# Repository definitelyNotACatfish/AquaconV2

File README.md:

# Web based Aquarium LED controller
I didn't want to pay 200€ to buy a 6 channel LED PWM controller. So I invested 400€ and a half year to build it myself :)

## Keyfeatures
- 6 channels PWM controlled (For LEDs and other stuff like CO2 relay or PC fan to cool water surface
- Web based interface to set up channel independent scenarious
- Temperature controlled water surface cooling (Really cool in summer)
- SD card bootloader and ethernet based file transfer to SD card

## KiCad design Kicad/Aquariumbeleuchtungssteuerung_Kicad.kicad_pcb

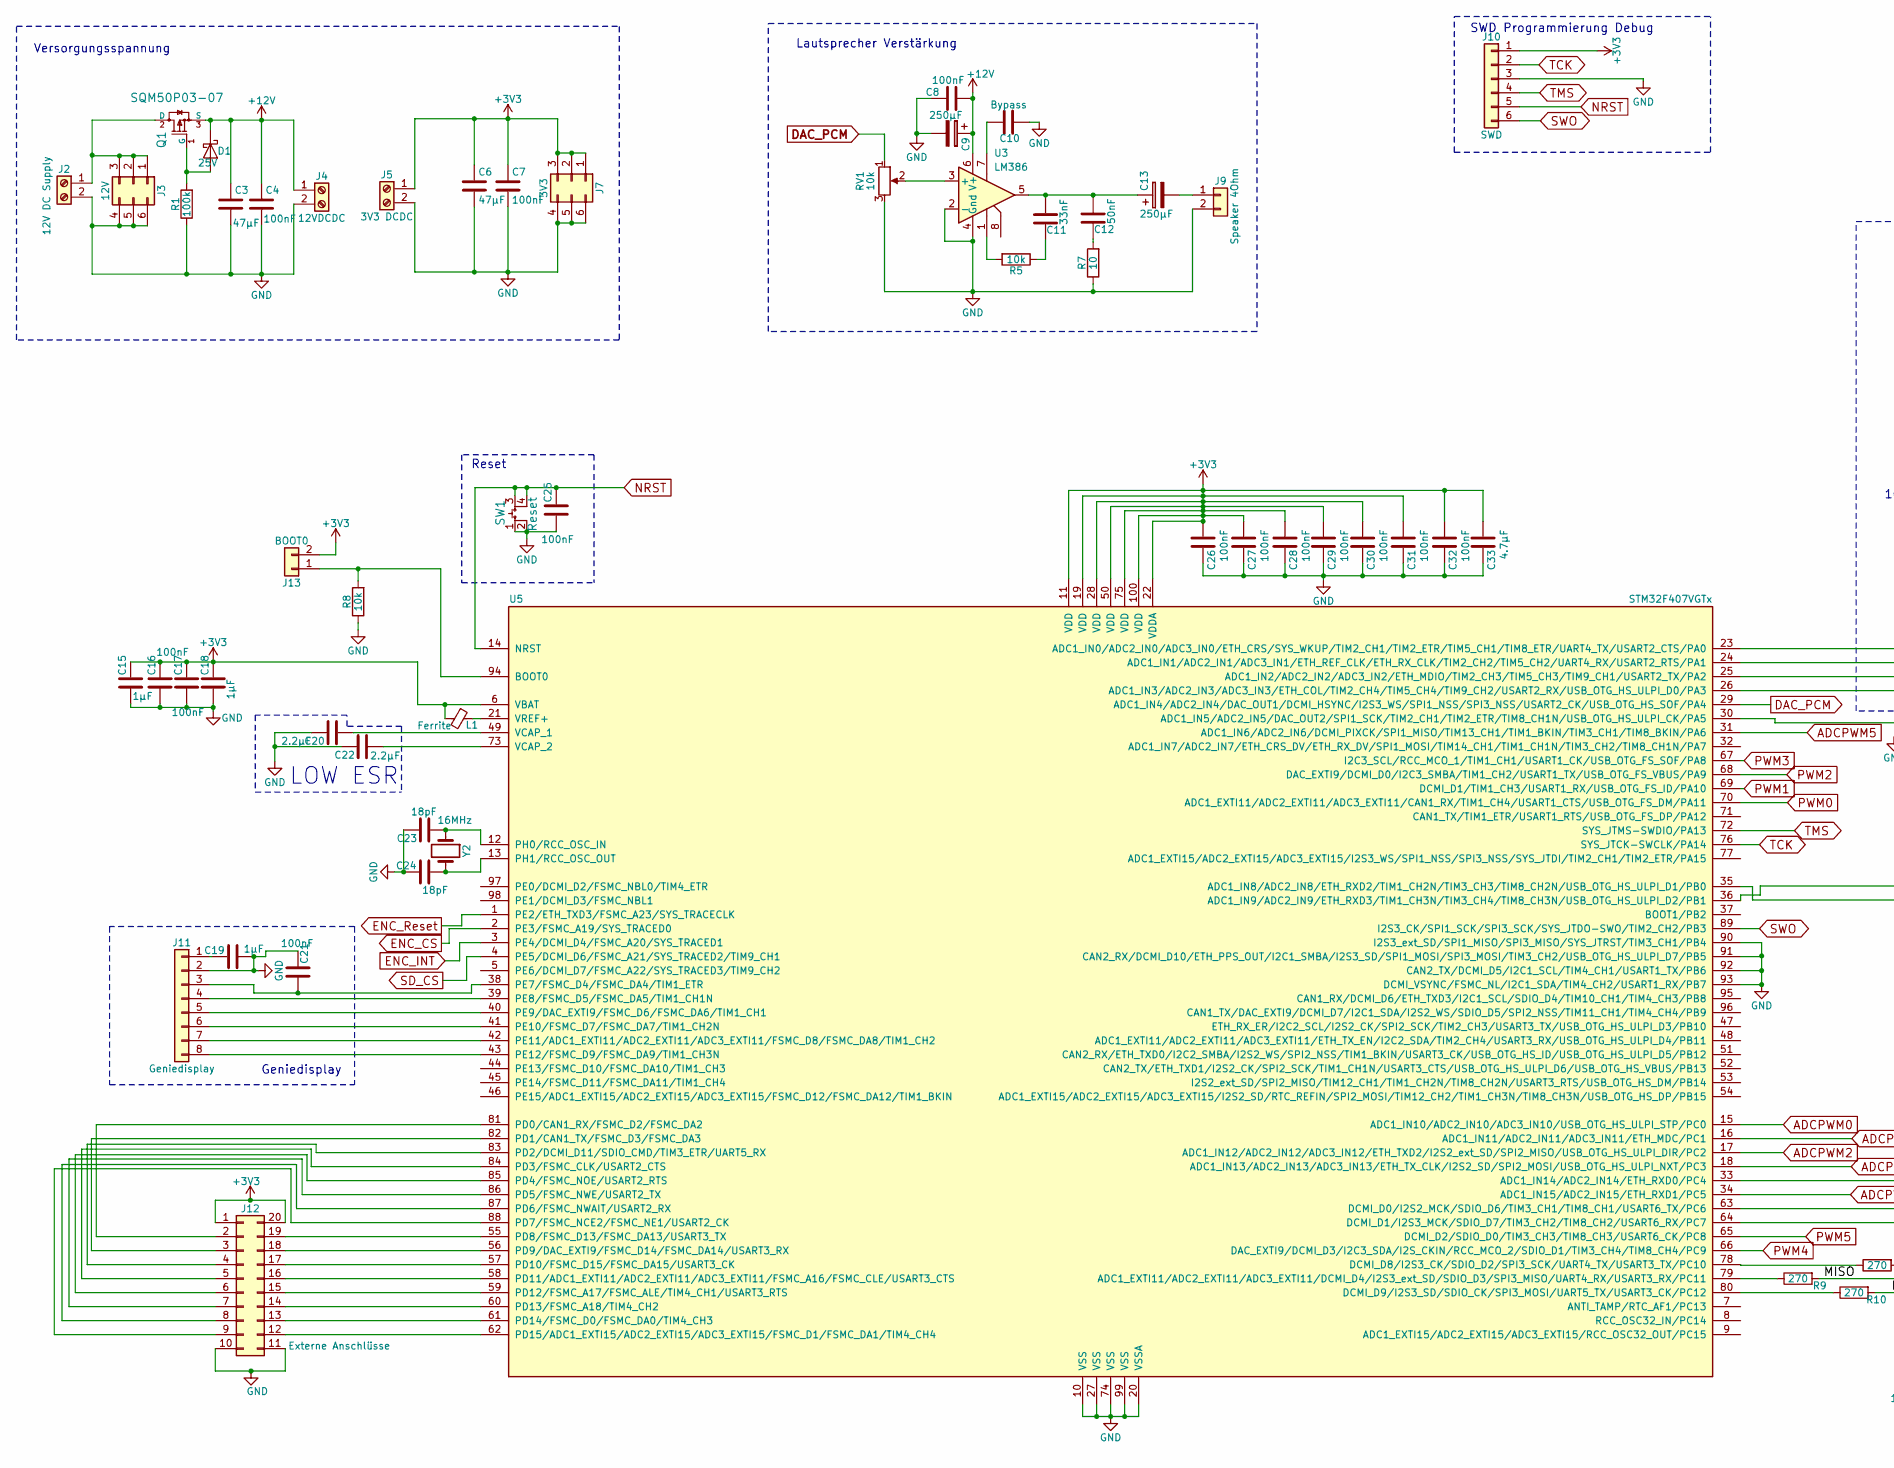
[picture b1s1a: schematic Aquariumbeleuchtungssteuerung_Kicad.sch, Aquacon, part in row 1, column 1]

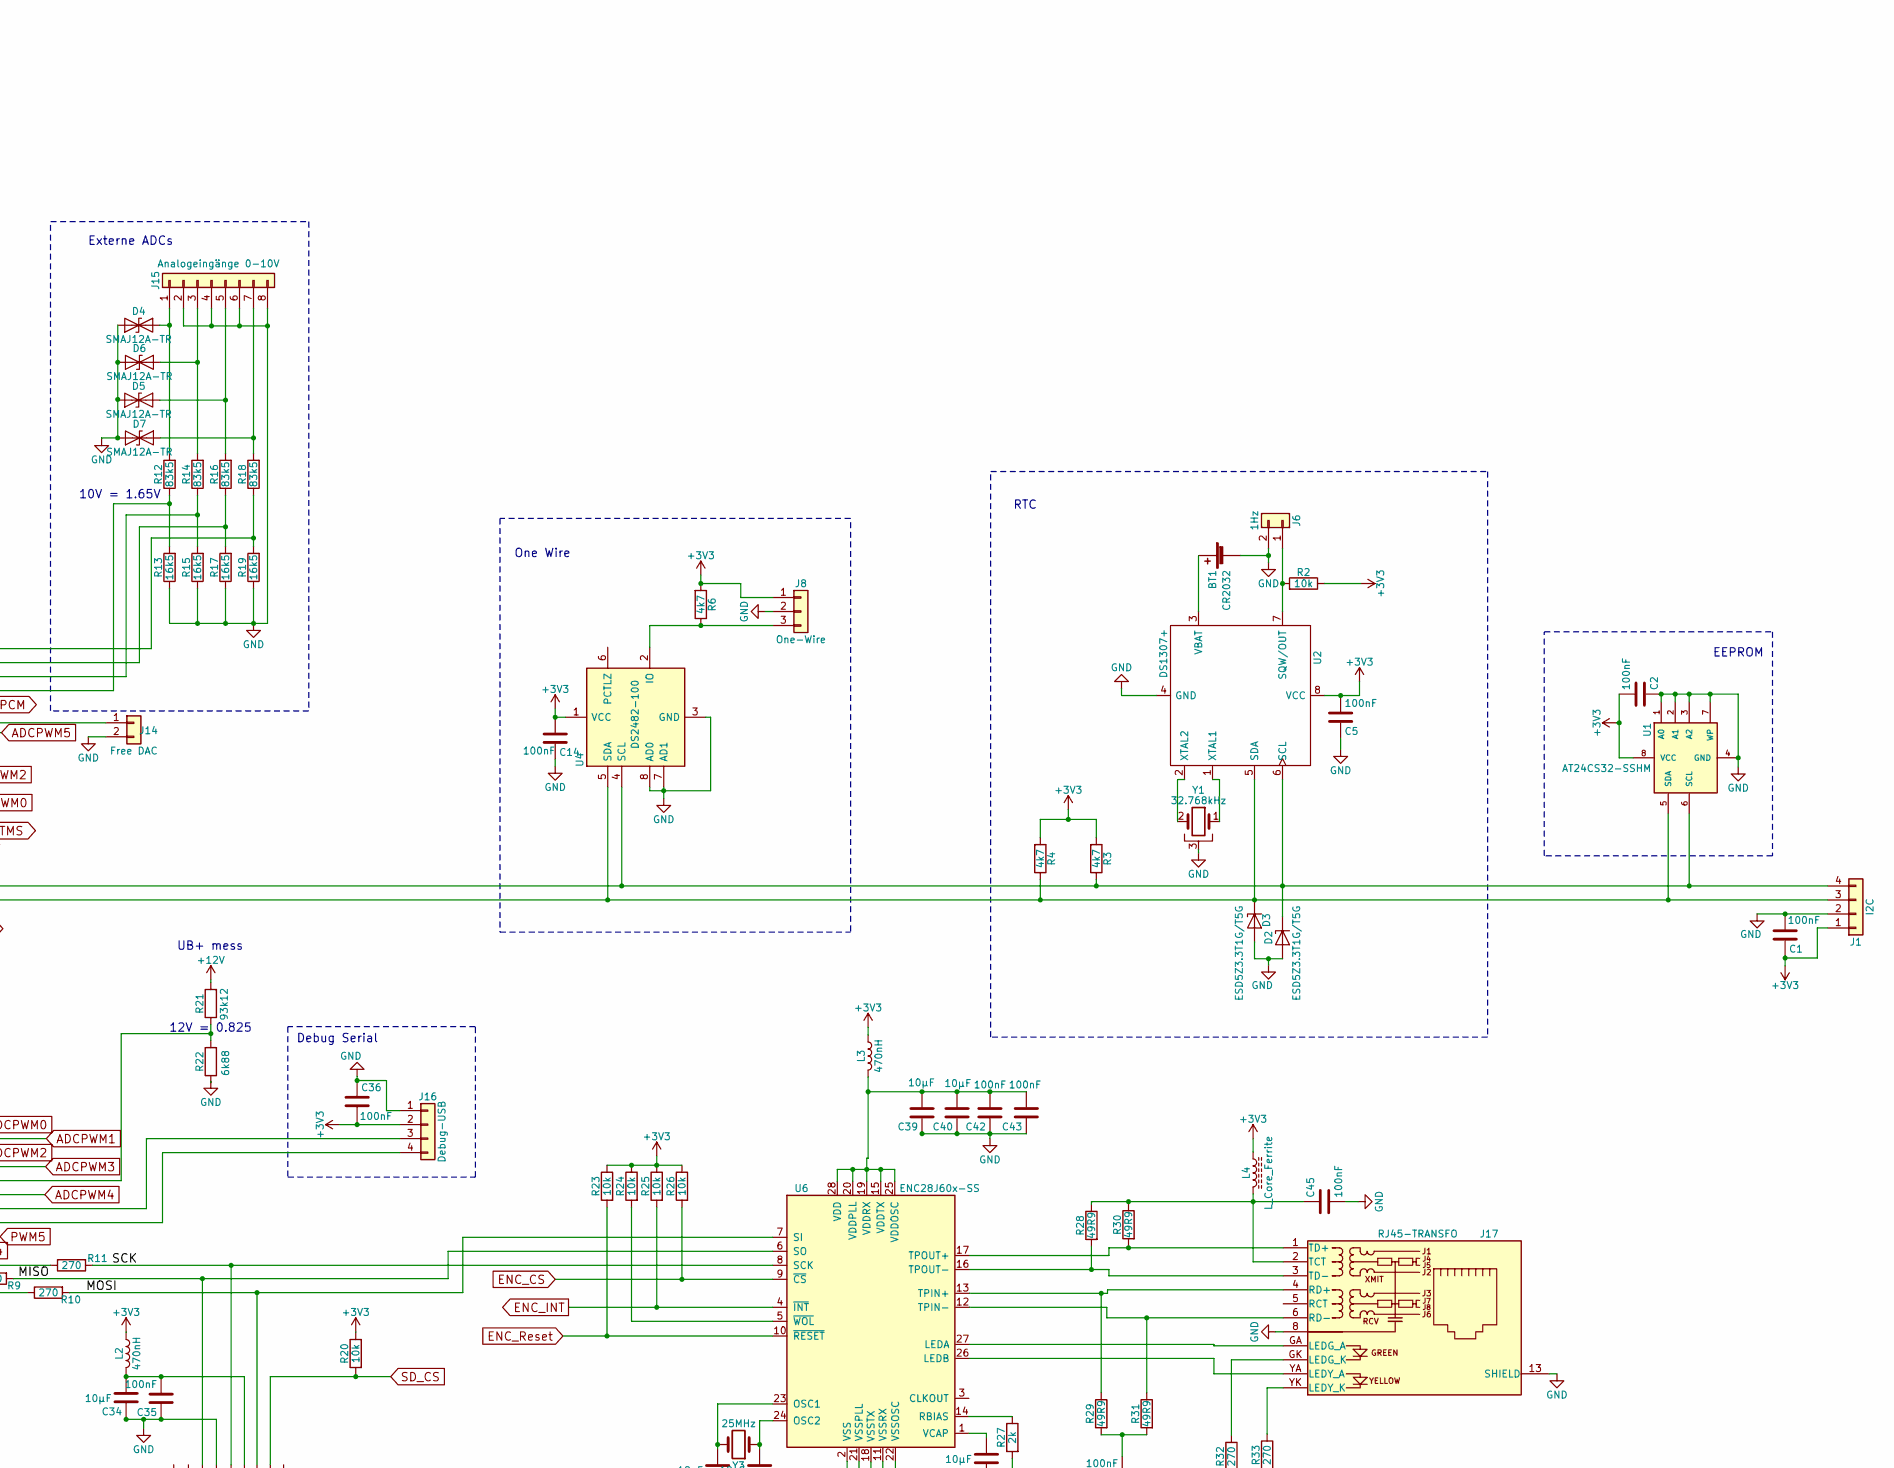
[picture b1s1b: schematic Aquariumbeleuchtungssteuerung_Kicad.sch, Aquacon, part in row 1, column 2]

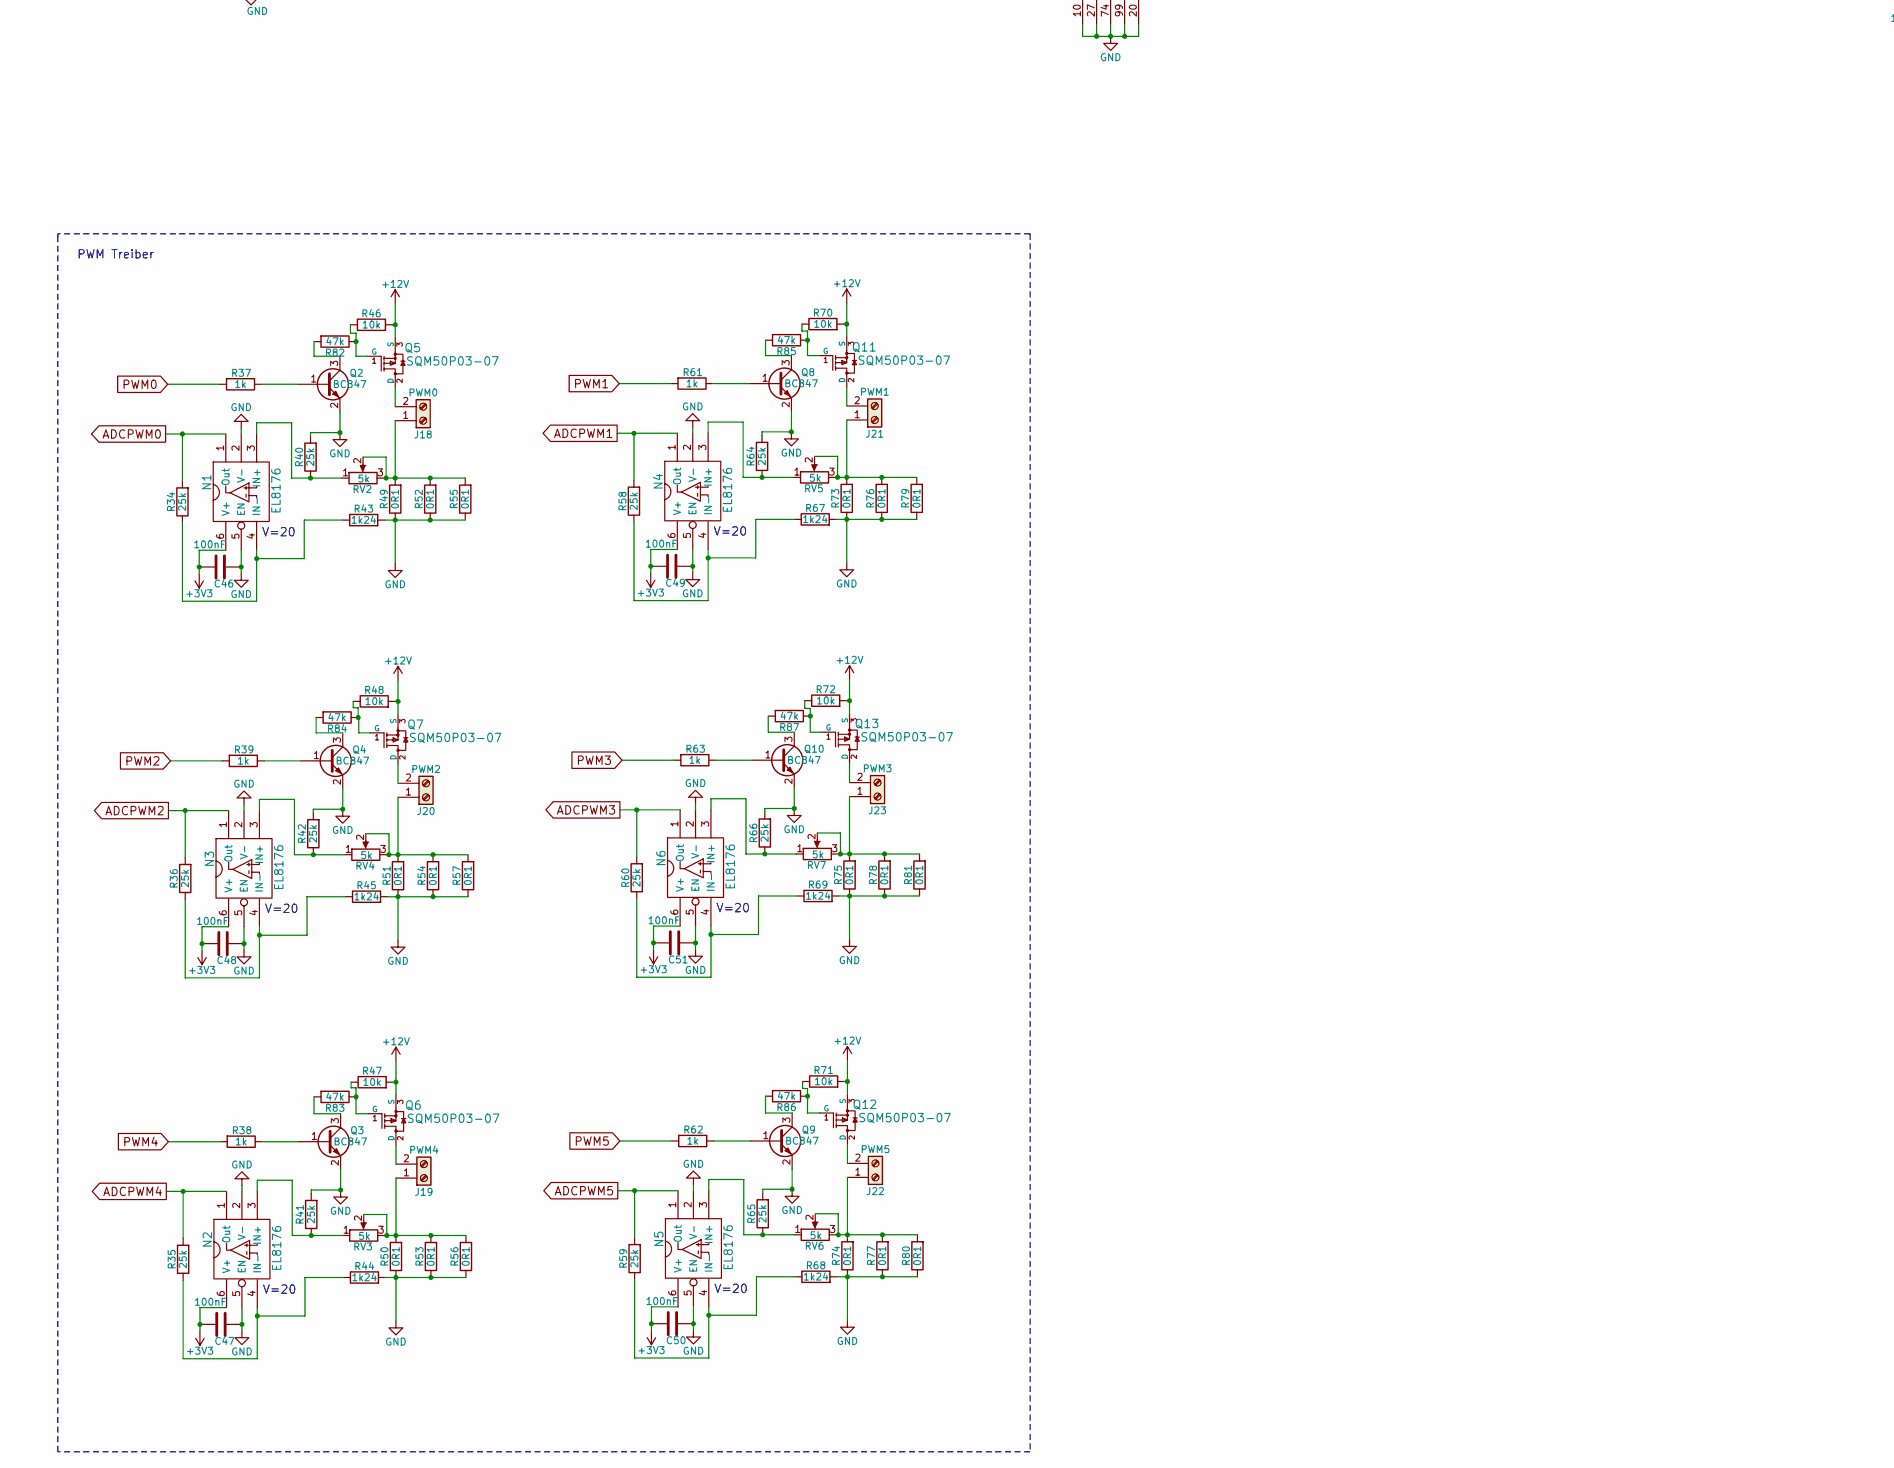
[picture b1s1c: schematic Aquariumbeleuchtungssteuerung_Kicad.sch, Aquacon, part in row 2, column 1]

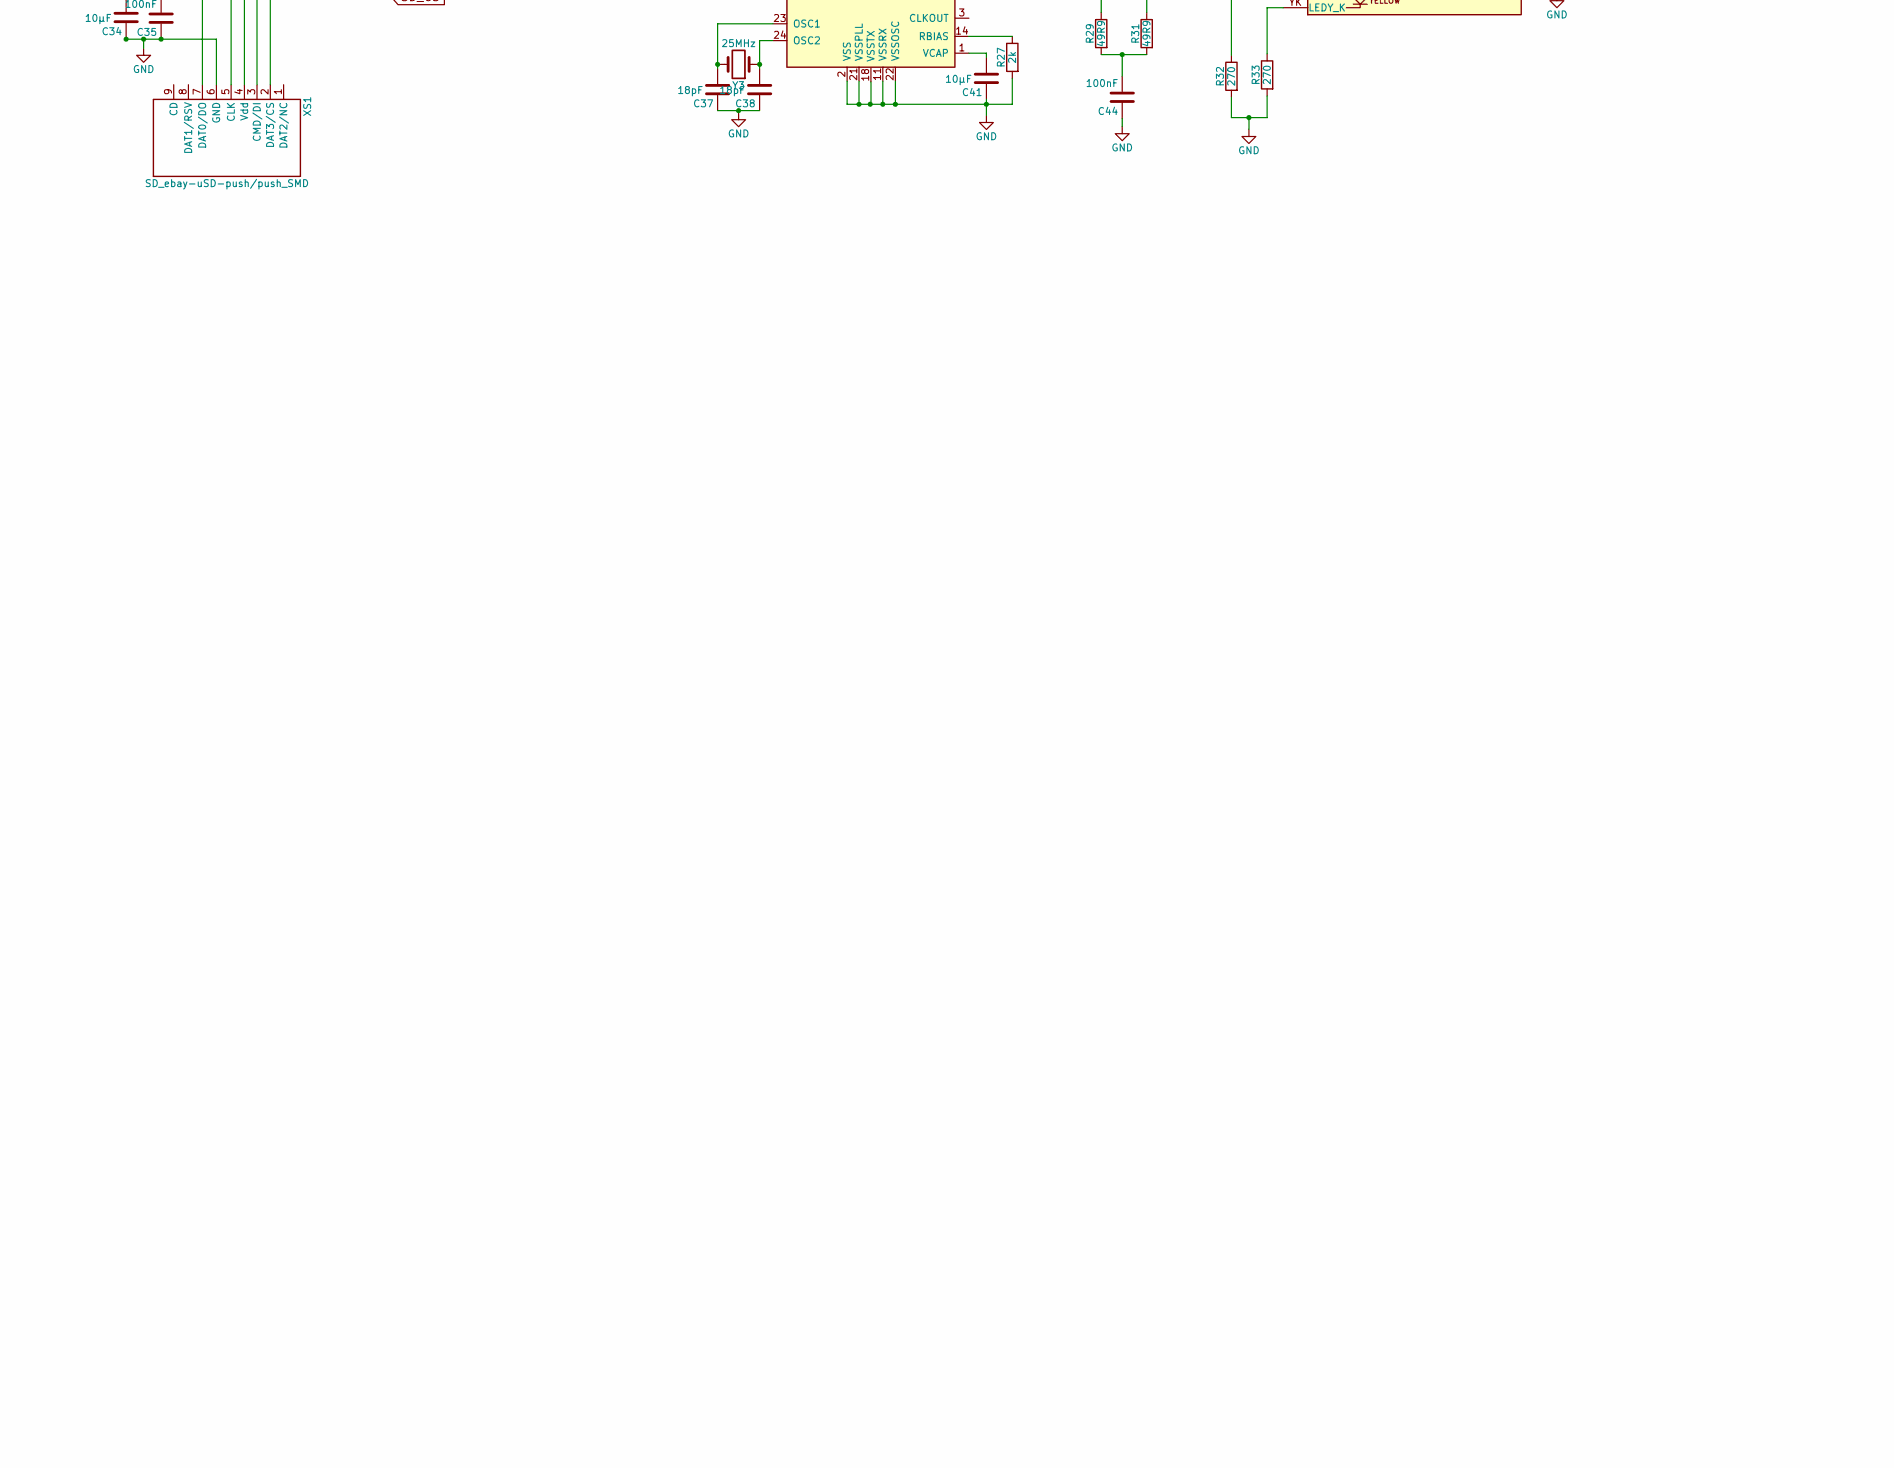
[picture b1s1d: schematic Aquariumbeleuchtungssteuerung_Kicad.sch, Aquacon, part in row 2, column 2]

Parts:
BT1: CR2032; Keystone_105_1x2430-CoinCell
C1, C2, C14, C21, C26, C27, C28, C29, C30, C31, C32, C36, C42, C43, C44, C45, C46, C47, C48, C49, C50, C51: 100nF; C_0603
C3, C6: 47µF; R_1206
C4, C5, C7, C8, C16, C17, C25: 100nF; C_0805
C9, C13: 250µF; CP_Tantalum_Case-X_EIA-7343-43_Reflow
C10: Bypass; C_0805
C11: 33nF; C_0805
C12: 50nF; C_0805
C15, C18, C19: 1µF; C_0805
C20, C22: 2.2µF; C_0805
C23, C24, C37, C38: 18pF; C_0603
C33: 4.7µF; C_0805
C34: 10µF; L_0805
C35: 100nF; L_0603
C39, C40, C41: 10µF; C_0805
D1: 25V; D_SOD-123
D2, D3: ESD5Z3.3T1G/T5G; D_SOD-523
D4, D5, D6, D7: SMAJ12A-TR; D_SMA
J1: I2C; Pin_Header_Straight_1x04_Pitch2.54mm
J2: 12V DC Supply; DECA_MB91_9.52mm_01X02
J3: 12V; Stiftleiste-2x3x2.54mm
J4: 12VDCDC; Pin_Header_Straight_1x02_Pitch2.54mm
J5: 3V3 DCDC; Pin_Header_Straight_1x02_Pitch2.54mm
J6: 1Hz; Pin_Header_Straight_1x02_Pitch2.54mm
J7: 3V3; Stiftleiste-2x3x2.54mm
J8: One-Wire; Pin_Header_Straight_1x03_Pitch2.54mm
J9: Speaker 4Ohm; Pin_Header_Straight_1x02_Pitch2.54mm
J10: SWD; Pin_Header_Straight_1x06_Pitch2.54mm
J11: Geniedisplay; Pin_Header_Straight_1x08_Pitch2.54mm
J12: Externe Anschlüsse; Stiftleiste_02x10
J13: BOOT0; GS2
J14: Free DAC; Pin_Header_Straight_1x02_Pitch2.54mm
J15: Analogeingänge 0-10V; TerminalBlock_bornier-8_P5.08mm
J16: Debug-USB; Pin_Header_Straight_1x04_Pitch2.54mm
J17: RJ45-TRANSFO; RJ45_TRANSFO
J18: PWM0; Phoenix-D-FRONT-2.5Vx2
J19: PWM4; Phoenix-D-FRONT-2.5Vx2
J20: PWM2; Phoenix-D-FRONT-2.5Vx2
J21: PWM1; Phoenix-D-FRONT-2.5Vx2
J22: PWM5; Phoenix-D-FRONT-2.5Vx2
J23: PWM3; Phoenix-D-FRONT-2.5Vx2
L1: Ferrite; L_0805
L2: 470nH; L_0805
L3: 470nH; L_0603
L4: L_Core_Ferrite; L_0603
N1, N2, N3, N4, N5, N6: EL8176; SOT-23-6_Handsoldering
Q1, Q5, Q6, Q7, Q11, Q12, Q13: SQM50P03-07; TO-263-2
Q2, Q3, Q4, Q8, Q9, Q10: BC847; SOT-23
R1: 100k; R_0805
R2, R8, R20, R23, R24, R25, R26: 10k; R_0603
R3, R4, R6: 4k7; R_0603
R5, R46, R47, R48, R70, R71, R72: 10k; R_0805
R7: 10; R_0805
R9, R10, R11, R32, R33: 270; R_0603
R12, R14, R16, R18: 83k5; R_0603
R13, R15, R17, R19: 16k5; R_0603
R21: 93k12; R_0805
R22: 6k88; R_0805
R27: 2k; R_0603
R28, R29, R30, R31: 49R9; R_0603
R34, R35, R36, R40, R41, R42, R58, R59, R60, R64, R65, R66: 25k; R_0603
R37, R38, R39, R61, R62, R63: 1k; R_0603
R43, R44, R45, R67, R68, R69: 1k24; R_0603
R49, R50, R51, R52, R53, R54, R55, R56, R57, R73, R74, R75, R76, R77, R78, R79, R80, R81: 0R1; R_1206
R82, R83, R84, R85, R86, R87: 47k; R_0603
RV1: 10k; Potentiometer_Trimmer_Bourns_3224J
RV2, RV3, RV4, RV5, RV6, RV7: 5k; Potentiometer_Trimmer_Bourns_3224J
SW1: Reset; SW_TH_Tactile_Omron_B3F-10xx
U1: AT24CS32-SSHM; SOIC-8_3.9x4.9mm_Pitch1.27mm
U2: DS1307+; SO-8_5.3x6.2mm_Pitch1.27mm
U3: LM386; DIP-8_W7.62mm_Socket
U4: DS2482-100; SOIC-8_3.9x4.9mm_Pitch1.27mm
U5: STM32F407VGTx; LQFP-100_14x14mm_Pitch0.5mm
U6: ENC28J60x-SS; SSOP-28_5.3x10.2mm_Pitch0.65mm
XS1: SD_ebay-uSD-push/push_SMD; Conn_uSDcard
Y1: 32.768kHz; Crystal_C38-LF_d3.0mm_l8.0mm_Horizontal_1EP_style2
Y2: 16MHz; Crystal_SMD_HC49-SD
Y3: 25MHz; Crystal_SMD_HC49-SD

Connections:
+3V3: C1.1, C2.2, C5.2, C6.1, C7.1, C14.2, C15.1, C16.1, C17.1, C18.1, C26.2, C27.2, C28.2, C29.2, C30.2, C31.2, C32.2, C33.2, C36.2, C46.2, C47.2, C48.2, C49.2, C50.2, C51.2, J1.1, J5.1, J7.1, J7.2, J7.3, J8.1, J10.1, J12.1, J12.20, J13.2, J16.2, L1.2, L2.1, L3.1, L4.1, N1.6 (V+), N2.6 (V+), N3.6 (V+), N4.6 (V+), N5.6 (V+), N6.6 (V+), R2.1, R3.2, R4.2, R6.2, R20.1, R23.1, R24.1, R25.1, R26.1, U1.8 (VCC), U2.8 (VCC), U4.1 (VCC), U5.6 (VBAT), U5.11 (VDD), U5.19 (VDD), U5.22 (VDDA), U5.28 (VDD), U5.50 (VDD), U5.75 (VDD), U5.100 (VDD)
+12V: C3.1, C4.1, C8.1, C9.1, D1.1 (K), J4.1, Q1.3 (S), Q5.3 (S), Q6.3 (S), Q7.3 (S), Q11.3 (S), Q12.3 (S), Q13.3 (S), R21.2, R46.2, R47.2, R48.2, R70.2, R71.2, R72.2, U3.6 (V+)
/MISO: R9.2, U6.6 (SO), XS1.7 (DAT0/DO)
/MOSI: R10.2, U6.7 (SI), XS1.3 (CMD/DI)
/SCK: R11.2, U6.8 (SCK), XS1.5 (CLK)
ADCPWM0: N1.1 (Out), R34.2, U5.15 (ADC1_IN10/ADC2_IN10/ADC3_IN10/USB_OTG_H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)
ADCPWM1: N4.1 (Out), R58.2, U5.16 (ADC1_IN11/ADC2_IN11/ADC3_IN11/ETH_MDC/P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)
ADCPWM2: N3.1 (Out), R36.2, U5.17 (ADC1_IN12/ADC2_IN12/ADC3_IN12/ETH_TXD2/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)
ADCPWM3: N6.1 (Out), R60.2, U5.18 (ADC1_IN13/ADC2_IN13/ADC3_IN13/ETH_TX_CL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)
ADCPWM4: N2.1 (Out), R35.2, U5.34 (ADC1_IN15/ADC2_IN15/ETH_RXD1/PC5)
ADCPWM5: N5.1 (Out), R59.2, U5.31 (ADC1_IN6/ADC2_IN6/DCMI_PIXCK/SPI1_MISO/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)
DAC_PCM: RV1.1, U5.29 (ADC1_IN4/ADC2_IN4/DAC_OUT1/DCMI_HSYNC/I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)
ENC_CS: R26.2, U5.2 (PE3/FSMC_A19/SYS_TRACED0), U6.9 (~CS)
ENC_INT: R25.2, U5.3 (PE4/DCMI_D4/FSMC_A20/SYS_TRACED1), U6.4 (~INT)
ENC_Reset: R23.2, U5.1 (PE2/ETH_TXD3/FSMC_A23/SYS_TRACECLK), U6.10 (~RESET)
GND: BT1.2 (-), C1.2, C2.1, C3.2, C4.2, C5.1, C6.2, C7.2, C8.2, C9.2, C10.2, C14.1, C15.2, C16.2, C17.2, C18.2, C19.2, C20.1, C21.1, C22.1, C23.1, C24.1, C25.2, C26.1, C27.1, C28.1, C29.1, C30.1, C31.1, C32.1, C33.1, C34.1, C35.1, C36.1, C37.1, C38.1, C39.1, C40.1, C41.1, C42.1, C43.1, C44.1, C45.2, C46.1, C47.1, C48.1, C49.1, C50.1, C51.1, D2.2 (A), D3.2 (A), D4.1 (A1), D5.1 (A1), D6.1 (A1), D7.1 (A1), J1.2, J2.2, J3.4, J3.5, J3.6, J4.2, J5.2, J6.2, J7.4, J7.5, J7.6, J8.2, J9.2, J10.3, J11.2, J12.10, J12.11, J14.2, J15.2, J15.4, J15.6, J15.8, J16.1, J17.8, J17.13 (SHIELD), N1.2 (V-), N1.5 (EN), N2.2 (V-), N2.5 (EN), N3.2 (V-), N3.5 (EN), N4.2 (V-), N4.5 (EN), N5.2 (V-), N5.5 (EN), N6.2 (V-), N6.5 (EN), Q2.2 (E), Q3.2 (E), Q4.2 (E), Q8.2 (E), Q9.2 (E), Q10.2 (E), R1.1, R7.1, R8.1, R13.1, R15.1, R17.1, R19.1, R22.1, R27.2, R32.2, R33.2, R40.2, R41.2, R42.2, R43.2, R44.2, R45.2, R49.1, R50.1, R51.1, R52.1, R53.1, R54.1, R55.1, R56.1, R57.1, R64.2, R65.2, R66.2, R67.2, R68.2, R69.2, R73.1, R74.1, R75.1, R76.1, R77.1, R78.1, R79.1, R80.1, R81.1, RV1.3, SW1.1, SW1.2, U1.1 (A0), U1.2 (A1), U1.3 (A2), U1.4 (GND), U1.7 (WP), U2.4 (GND), U3.2 (-), U3.4 (Gnd), U4.3 (GND), U4.7 (AD1), U4.8 (AD0), U5.10 (VSS), U5.20 (VSSA), U5.27 (VSS), U5.74 (VSS), U5.90 (I2S3_ext_SD/SPI1_MISO/SPI3_MISO/SYS_JTR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), U5.91 (CAN2_RX/DCMI_D10/ETH_PPS_OUT/I2C1_SMBA/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), U5.92 (CAN2_TX/DCMI_D5/I2C1_SCL/TIM4_CH1/USART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), U5.93 (DCMI_VSYNC/FSMC_NL/I2C1_SDA/TIM4_CH2/US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), U5.99 (VSS), U6.2 (VSS), U6.11 (VSSRX), U6.18 (VSSTX), U6.21 (VSSPLL), U6.22 (VSSOSC), XS1.6 (GND), Y1.3
NRST: C25.1, J10.5, SW1.3, SW1.4, U5.14 (NRST)
unnamed: BT1.1 (+), U2.3 (VBAT)
unnamed: C10.1, U3.7
unnamed: C11.1, R5.1
unnamed: C11.2, C12.2, C13.1, U3.5
unnamed: C12.1, R7.2
unnamed: C13.2, J9.1
unnamed: C19.1, J11.1
unnamed: C20.2, U5.49 (VCAP_1)
unnamed: C21.2, J11.3, U5.38 (PE7/FSMC_D4/FSMC_DA4/TIM1_ETR)
unnamed: C22.2, U5.73 (VCAP_2)
unnamed: C23.2, U5.12 (PH0/RCC_OSC_IN), Y2.1
unnamed: C24.2, U5.13 (PH1/RCC_OSC_OUT), Y2.2
unnamed: C34.2, C35.2, L2.2, XS1.4 (Vdd)
unnamed: C37.2, U6.23 (OSC1), Y3.2
unnamed: C38.2, U6.24 (OSC2), Y3.1
unnamed: C39.2, C40.2, C42.2, C43.2, L3.2, U6.15 (VDDTX), U6.19 (VDDRX), U6.20 (VDDPLL), U6.25 (VDDOSC), U6.28 (VDD)
unnamed: C41.2, U6.1 (VCAP)
unnamed: C44.2, R29.2, R31.2
unnamed: C45.1, J17.2 (TCT), L4.2, R28.1, R30.1
unnamed: D1.2 (A), Q1.1 (G), R1.2
unnamed: D2.1 (K), J1.4, R3.1, U1.6 (SCL), U2.6 (SCL), U4.4 (SCL), U5.36 (ADC1_IN9/ADC2_IN9/ETH_RXD3/TIM1_CH3N/TI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)
unnamed: D3.1 (K), J1.3, R4.1, U1.5 (SDA), U2.5 (SDA), U4.5 (SDA), U5.35 (ADC1_IN8/ADC2_IN8/ETH_RXD2/TIM1_CH2N/TI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)
unnamed: D4.2 (A2), J15.1, R12.2
unnamed: D5.2 (A2), J15.5, R16.2
unnamed: D6.2 (A2), J15.3, R14.2
unnamed: D7.2 (A2), J15.7, R18.2
unnamed: J2.1, J3.1, J3.2, J3.3, Q1.2 (D)
unnamed: J6.1, R2.2, U2.7 (SQW/OUT)
unnamed: J8.3, R6.1, U4.2 (IO)
unnamed: J11.4, U5.39 (PE8/FSMC_D5/FSMC_DA5/TIM1_CH1N)
unnamed: J11.5, U5.40 (PE9/DAC_EXTI9/FSMC_D6/FSMC_DA6/TIM1_CH1)
unnamed: J11.6, U5.41 (PE10/FSMC_D7/FSMC_DA7/TIM1_CH2N)
unnamed: J11.7, U5.42 (PE11/ADC1_EXTI11/ADC2_EXTI11/ADC3_EXTI1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)
unnamed: J11.8, U5.43 (PE12/FSMC_D9/FSMC_DA9/TIM1_CH3N)
unnamed: J12.2, U5.81 (PD0/CAN1_RX/FSMC_D2/FSMC_DA2)
unnamed: J12.3, U5.82 (PD1/CAN1_TX/FSMC_D3/FSMC_DA3)
unnamed: J12.4, U5.83 (PD2/DCMI_D11/SDIO_CMD/TIM3_ETR/UART5_RX)
unnamed: J12.5, U5.84 (PD3/FSMC_CLK/USART2_CTS)
unnamed: J12.6, U5.85 (PD4/FSMC_NOE/USART2_RTS)
unnamed: J12.7, U5.86 (PD5/FSMC_NWE/USART2_TX)
unnamed: J12.8, U5.87 (PD6/FSMC_NWAIT/USART2_RX)
unnamed: J12.9, U5.88 (PD7/FSMC_NCE2/FSMC_NE1/USART2_CK)
unnamed: J12.12, U5.62 (PD15/ADC1_EXTI15/ADC2_EXTI15/ADC3_EXTI1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)
unnamed: J12.13, U5.61 (PD14/FSMC_D0/FSMC_DA0/TIM4_CH3)
unnamed: J12.14, U5.60 (PD13/FSMC_A18/TIM4_CH2)
unnamed: J12.15, U5.59 (PD12/FSMC_A17/FSMC_ALE/TIM4_CH1/USART3_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)
unnamed: J12.16, U5.58 (PD11/ADC1_EXTI11/ADC2_EXTI11/ADC3_EXTI1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)
unnamed: J12.17, U5.57 (PD10/FSMC_D15/FSMC_DA15/USART3_CK)
unnamed: J12.18, U5.56 (PD9/DAC_EXTI9/FSMC_D14/FSMC_DA14/USART3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)
unnamed: J12.19, U5.55 (PD8/FSMC_D13/FSMC_DA13/USART3_TX)
unnamed: J13.1, R8.2, U5.94 (BOOT0)
unnamed: J14.1, U5.30 (ADC1_IN5/ADC2_IN5/DAC_OUT2/SPI1_SCK/TIM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)
unnamed: J16.3, U5.63 (DCMI_D0/I2S2_MCK/SDIO_D6/TIM3_CH1/TIM8_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)
unnamed: J16.4, U5.64 (DCMI_D1/I2S3_MCK/SDIO_D7/TIM3_CH2/TIM8_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)
unnamed: J17.1 (TD+), R30.2, U6.17 (TPOUT+)
unnamed: J17.3 (TD-), R28.2, U6.16 (TPOUT-)
unnamed: J17.4 (RD+), R29.1, U6.13 (TPIN+)
unnamed: J17.6 (RD-), R31.1, U6.12 (TPIN-)
unnamed: J17.GA (LEDG_A), U6.27 (LEDA)
unnamed: J17.GK (LEDG_K), R32.1
unnamed: J17.YA (LEDY_A), U6.26 (LEDB)
unnamed: J17.YK (LEDY_K), R33.1
unnamed: J18.1, R49.2, R52.2, R55.2, RV2.2, RV2.3
unnamed: J18.2, Q5.2 (D)
unnamed: J19.1, R50.2, R53.2, R56.2, RV3.2, RV3.3
unnamed: J19.2, Q6.2 (D)
unnamed: J20.1, R51.2, R54.2, R57.2, RV4.2, RV4.3
unnamed: J20.2, Q7.2 (D)
unnamed: J21.1, R73.2, R76.2, R79.2, RV5.2, RV5.3
unnamed: J21.2, Q11.2 (D)
unnamed: J22.1, R74.2, R77.2, R80.2, RV6.2, RV6.3
unnamed: J22.2, Q12.2 (D)
unnamed: J23.1, R75.2, R78.2, R81.2, RV7.2, RV7.3
unnamed: J23.2, Q13.2 (D)
unnamed: L1.1, U5.21 (VREF+)
unnamed: N1.3 (IN+), R40.1, RV2.1
unnamed: N1.4 (IN-), R34.1, R43.1
unnamed: N2.3 (IN+), R41.1, RV3.1
unnamed: N2.4 (IN-), R35.1, R44.1
unnamed: N3.3 (IN+), R42.1, RV4.1
unnamed: N3.4 (IN-), R36.1, R45.1
unnamed: N4.3 (IN+), R64.1, RV5.1
unnamed: N4.4 (IN-), R58.1, R67.1
unnamed: N5.3 (IN+), R65.1, RV6.1
unnamed: N5.4 (IN-), R59.1, R68.1
unnamed: N6.3 (IN+), R66.1, RV7.1
unnamed: N6.4 (IN-), R60.1, R69.1
unnamed: Q2.1 (B), R37.1
unnamed: Q2.3 (C), R82.2
unnamed: Q3.1 (B), R38.1
unnamed: Q3.3 (C), R83.2
unnamed: Q4.1 (B), R39.1
unnamed: Q4.3 (C), R84.2
unnamed: Q5.1 (G), R46.1, R82.1
unnamed: Q6.1 (G), R47.1, R83.1
unnamed: Q7.1 (G), R48.1, R84.1
unnamed: Q8.1 (B), R61.1
unnamed: Q8.3 (C), R85.2
unnamed: Q9.1 (B), R62.1
unnamed: Q9.3 (C), R86.2
unnamed: Q10.1 (B), R63.1
unnamed: Q10.3 (C), R87.2
unnamed: Q11.1 (G), R70.1, R85.1
unnamed: Q12.1 (G), R71.1, R86.1
unnamed: Q13.1 (G), R72.1, R87.1
unnamed: R5.2, U3.1
unnamed: R9.1, U5.79 (ADC1_EXTI11/ADC2_EXTI11/ADC3_EXTI11/DCM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)
unnamed: R10.1, U5.80 (DCMI_D9/I2S3_SD/SDIO_CK/SPI3_MOSI/UART5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)
unnamed: R11.1, U5.78 (DCMI_D8/I2S3_CK/SDIO_D2/SPI3_SCK/UART4_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)
unnamed: R12.1, R13.2, U5.26 (ADC1_IN3/ADC2_IN3/ADC3_IN3/ETH_COL/TIM2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)
unnamed: R14.1, R15.2, U5.25 (ADC1_IN2/ADC2_IN2/ADC3_IN2/ETH_MDIO/TIM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)
unnamed: R16.1, R17.2, U5.24 (ADC1_IN1/ADC2_IN1/ADC3_IN1/ETH_REF_CLK/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)
unnamed: R18.1, R19.2, U5.23 (ADC1_IN0/ADC2_IN0/ADC3_IN0/ETH_CRS/SYS_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)
unnamed: R21.1, R22.2, U5.33 (ADC1_IN14/ADC2_IN14/ETH_RXD0/PC4)
unnamed: R24.2, U6.5 (~WOL)
unnamed: R27.1, U6.14 (RBIAS)
unnamed: RV1.2, U3.3 (+)
unnamed: U2.1 (XTAL1), Y1.1
unnamed: U2.2 (XTAL2), Y1.2
PWM0: R37.2, U5.70 (ADC1_EXTI11/ADC2_EXTI11/ADC3_EXTI11/CAN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)
PWM1: R61.2, U5.69 (DCMI_D1/TIM1_CH3/USART1_RX/USB_OTG_FS_I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)
PWM2: R39.2, U5.68 (DAC_EXTI9/DCMI_D0/I2C3_SMBA/TIM1_CH2/US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)
PWM3: R63.2, U5.67 (I2C3_SCL/RCC_MCO_1/TIM1_CH1/USART1_CK/U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)
PWM4: R38.2, U5.66 (DAC_EXTI9/DCMI_D3/I2C3_SDA/I2S_CKIN/RCC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)
PWM5: R62.2, U5.65 (DCMI_D2/SDIO_D0/TIM3_CH3/TIM8_CH3/USART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)
SD_CS: R20.2, U5.4 (PE5/DCMI_D6/FSMC_A21/SYS_TRACED2/TIM9_C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), XS1.2 (DAT3/CS)
SWO: J10.6, U5.89 (I2S3_CK/SPI1_SCK/SPI3_SCK/SYS_JTDO-SWO/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)
TCK: J10.2, U5.76 (SYS_JTCK-SWCLK/PA14)
TMS: J10.4, U5.72 (SYS_JTMS-SWDIO/PA13)

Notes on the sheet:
12V = 0.825
UB+ mess
10V = 1.65V
PWM Treiber
Versorgungsspannung
V=20
Lautsprecher Verstärkung
V=20
Debug Serial
One Wire
RTC
EEPROM
LOW ESR
Reset
SWD Programmierung Debug
Geniedisplay
Externe ADCs

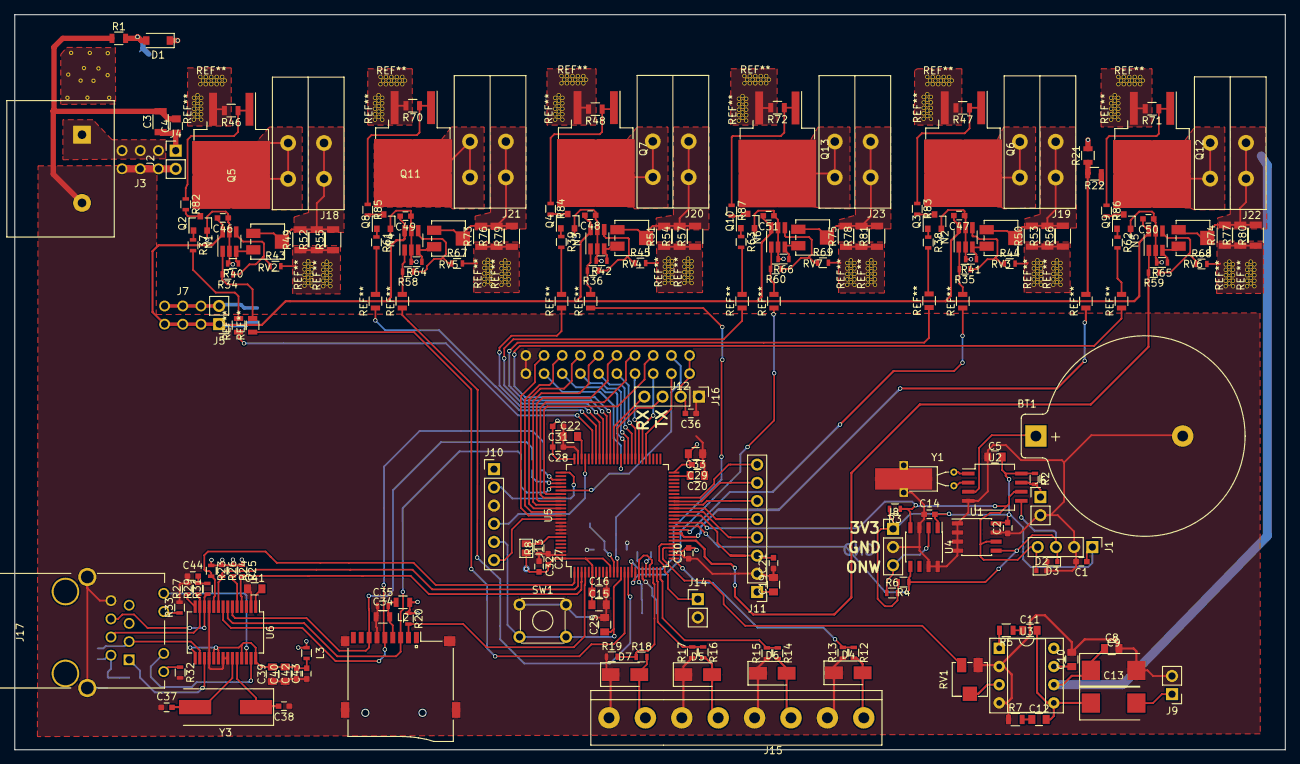
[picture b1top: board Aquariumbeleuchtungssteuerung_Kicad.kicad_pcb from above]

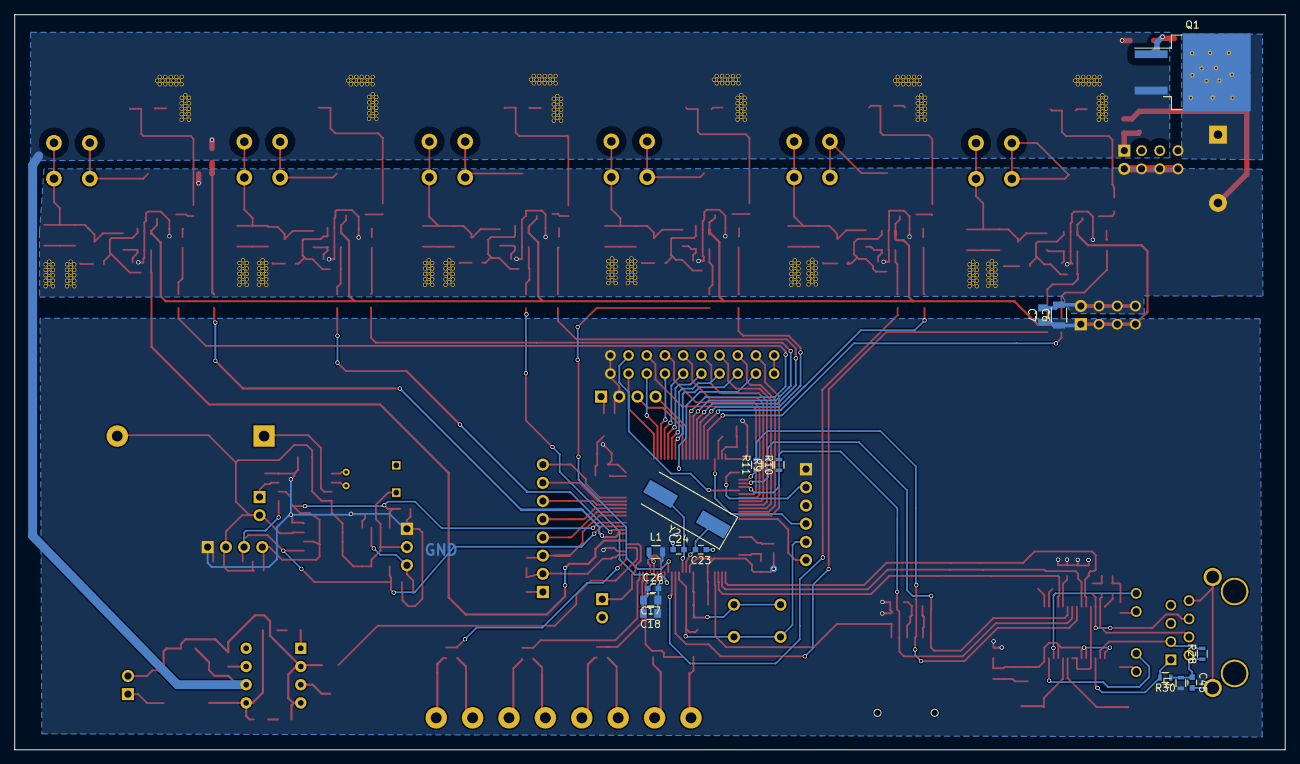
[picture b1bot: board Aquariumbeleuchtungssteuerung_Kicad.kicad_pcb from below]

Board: 2 copper layers, 177.4 x 102.6 mm, 210 parts (17 on the bottom side), 146 nets.

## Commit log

2025-12-10 Migration to Github
2025-12-10 Create LICENSE
